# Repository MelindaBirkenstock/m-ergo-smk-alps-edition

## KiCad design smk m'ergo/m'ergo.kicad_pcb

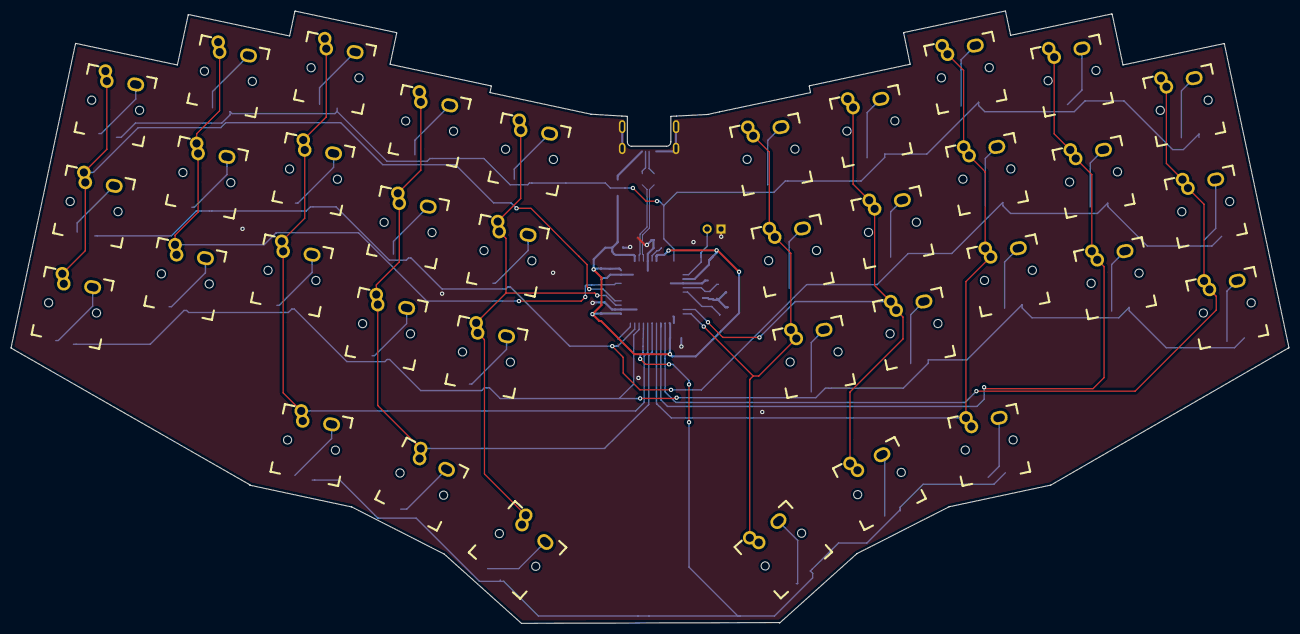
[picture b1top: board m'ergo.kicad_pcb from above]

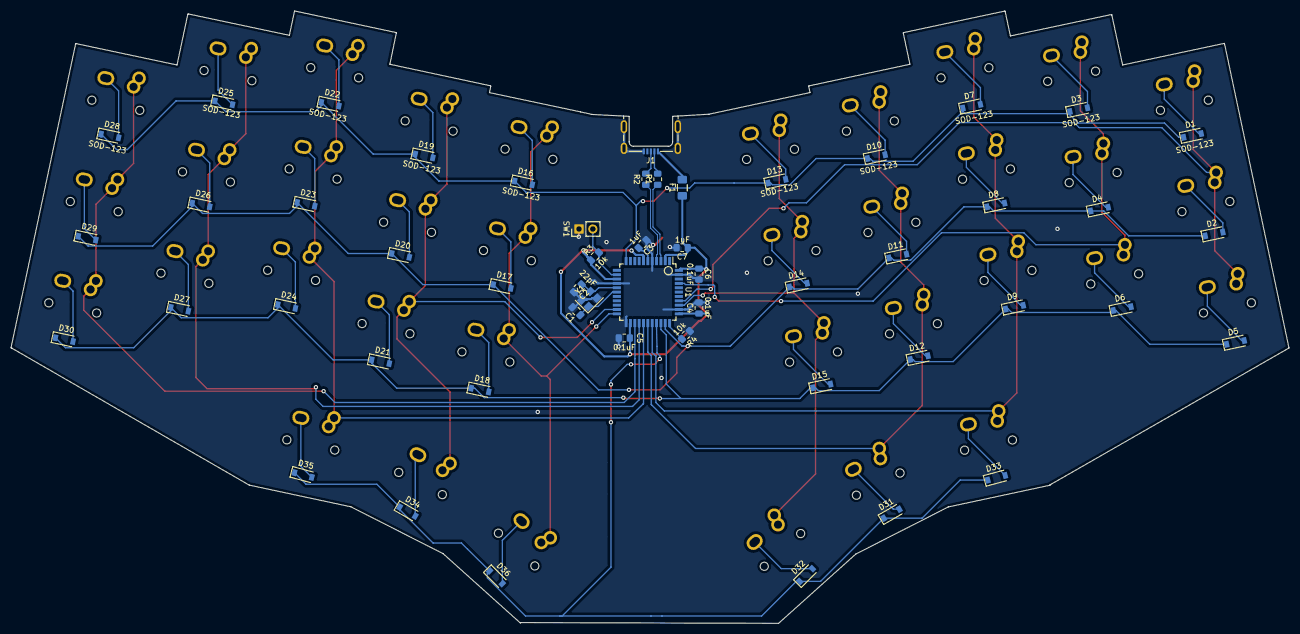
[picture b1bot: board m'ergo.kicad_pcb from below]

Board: 2 copper layers, 234.9 x 112.5 mm, 88 parts (52 on the bottom side), 62 nets.

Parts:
C1, C2: 22pF; C_0805_2012Metric_Pad1.15x1.40mm_HandSolder
C3, C7: 1uF; C_0805_2012Metric_Pad1.15x1.40mm_HandSolder
C4, C5, C6: 0.1uF; C_0805_2012Metric_Pad1.15x1.40mm_HandSolder
D1, D2, D3, D4, D5, D6, D7, D8, D9, D10, D11, D12, D13, D14, D15, D16, D17, D18, D19, D20, D21, D22, D23, D24, D25, D26, D27, D28, D29, D30, D31, D32, D33, D34, D35, D36: SOD-123; D_SOD-123-Pretty
F1: 500mA; Fuse_1206_3216Metric_Pad1.42x1.75mm_HandSolder
J1: USB_B_Micro; MOLEX_47642-0001_HandSoldering_cuts
MX1, MX2, MX3, MX4, MX5, MX7, MX8, MX9, MX10, MX11, MX12, MX13, MX14, MX15, MX16, MX17, MX18, MX19, MX20, MX21, MX22, MX23, MX24, MX25, MX26, MX27, MX28, MX29, MX30, MX31, MX32, MX33, MX34, MX35, MX36, MX37: MX-NoLED; fixedsmkalpspcbfootprint
R1, R2: 22; R_0805_2012Metric_Pad1.15x1.40mm_HandSolder
R3, R4: 10k; R_0805_2012Metric_Pad1.15x1.40mm_HandSolder
SW1: SW_Push; PinHeader_1x02_P2.54mm_Vertical
U1: ATmega32U4-AU; TQFP-44_10x10mm_P0.8mm
Y1: 16MHz; Crystal_SMD_3225-4Pin_3.2x2.5mm

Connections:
+5V: C4.1, C5.1, C6.1, C7.1, F1.1, R3.1, U1.2, U1.7, U1.14, U1.24, U1.34, U1.44
/DN+: R2.1, U1.4
/DN-: R1.1, U1.3
COL0: MX1.1, MX2.1, MX3.1, U1.37
COL1: MX4.1, MX5.1, MX7.1, U1.41
COL2: MX8.1, MX9.1, MX10.1, MX34.1, U1.29
COL3: MX11.1, MX12.1, MX13.1, MX32.1, U1.28
COL4: MX14.1, MX15.1, MX16.1, MX33.1, U1.36
COL5: MX17.1, MX18.1, MX19.1, MX37.1, U1.22
COL6: MX20.1, MX21.1, MX22.1, MX35.1, U1.21
COL7: MX23.1, MX24.1, MX25.1, MX36.1, U1.27
COL8: MX26.1, MX27.1, MX28.1, U1.26
COL9: MX29.1, MX30.1, MX31.1, U1.25
D+: J1.3, R2.2
D-: J1.2, R1.2
GND: C1.2, C2.2, C3.2, C4.2, C5.2, C6.2, C7.2, J1.5, J1.6, R4.1, SW1.1, U1.5, U1.15, U1.23, U1.35, U1.43, Y1.2, Y1.4
unnamed: C1.1, U1.17, Y1.1
unnamed: C2.1, U1.16, Y1.3
unnamed: C3.1, U1.6
unnamed: D1.2, MX1.2
unnamed: D2.2, MX2.2
unnamed: D3.2, MX4.2
unnamed: D4.2, MX5.2
unnamed: D5.2, MX3.2
unnamed: D6.2, MX7.2
unnamed: D7.2, MX8.2
unnamed: D8.2, MX9.2
unnamed: D9.2, MX10.2
unnamed: D10.2, MX11.2
unnamed: D11.2, MX12.2
unnamed: D12.2, MX13.2
unnamed: D13.2, MX14.2
unnamed: D14.2, MX15.2
unnamed: D15.2, MX16.2
unnamed: D16.2, MX17.2
unnamed: D17.2, MX18.2
unnamed: D18.2, MX19.2
unnamed: D19.2, MX20.2
unnamed: D20.2, MX21.2
unnamed: D21.2, MX22.2
unnamed: D22.2, MX23.2
unnamed: D23.2, MX24.2
unnamed: D24.2, MX25.2
unnamed: D25.2, MX26.2
unnamed: D26.2, MX27.2
unnamed: D27.2, MX28.2
unnamed: D28.2, MX29.2
unnamed: D29.2, MX30.2
unnamed: D30.2, MX31.2
unnamed: D31.2, MX32.2
unnamed: D32.2, MX33.2
unnamed: D33.2, MX34.2
unnamed: D34.2, MX35.2
unnamed: D35.2, MX36.2
unnamed: D36.2, MX37.2
unnamed: R3.2, SW1.2, U1.13
unnamed: R4.2, U1.33
ROW0: D1.1, D3.1, D7.1, D10.1, D13.1, D16.1, D19.1, D22.1, D25.1, D28.1, U1.11
ROW1: D2.1, D4.1, D8.1, D11.1, D14.1, D17.1, D20.1, D23.1, D26.1, D29.1, U1.32
ROW2: D5.1, D6.1, D9.1, D12.1, D15.1, D18.1, D21.1, D24.1, D27.1, D30.1, U1.31
ROW3: D31.1, D32.1, D33.1, D34.1, D35.1, D36.1, U1.30
VCC: F1.2, J1.1

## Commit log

2020-08-01 first push
    atreus style board yadd yadda, no promises this works/no promises the right libraries are even there. use the "fixedsmkalpsfootprint" in the keyboard.pretty library
2020-08-01 removed
    removed useless stuff that wasn't supposed to be there
